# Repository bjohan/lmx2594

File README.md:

# lmx2594
Test board for lmx2594. The PCB is connected to an Arduino nano which then can be controlled from a PC. The Arduino can be programmed so that the PLL always starts with a certain frequency. It is also possible to change frequency dynamically.

# PCB
Current version of PCB in pcb/lmx2594_v2/

# Arduino sketch
In lmx2594NewSketch/

# Python library commandline tool
In py/ 
```
/lmx2594cmd2.py --help
usage: lmx2594.py [-h] [-f FREQUENCY] [-r REFERENCE] [-mo MASH_ORDER] [-m] [-l] port

Program for controlling lmx2594 pll

positional arguments:
  port                  For instance /dev/ttyUSB0

options:
  -h, --help            show this help message and exit
  -f FREQUENCY, --frequency FREQUENCY
                        Set frequency
  -r REFERENCE, --reference REFERENCE
                        Reference frequency
  -mo MASH_ORDER, --mash-order MASH_ORDER
                        Order of delta sigma
  -m, --macro           Record macro while setting frequency that will be executed at boot. This means that the device will set the specified frequency during power on even without a
                        computer
  -l, --locked          Check lock status

Have fun!
```

Example:

Program arduino so it always starts at 1296MHz with 10MHz reference
```
./lmx2594cmd2.py /dev/ttyUSB0 -r 10e6 -f 1296e6 -m
```

Example:

Set the frequency to 144MHz with 10MHz reference
```
./lmx2594cmd2.py /dev/ttyUSB0 -r 10e6 -f 144e6
```

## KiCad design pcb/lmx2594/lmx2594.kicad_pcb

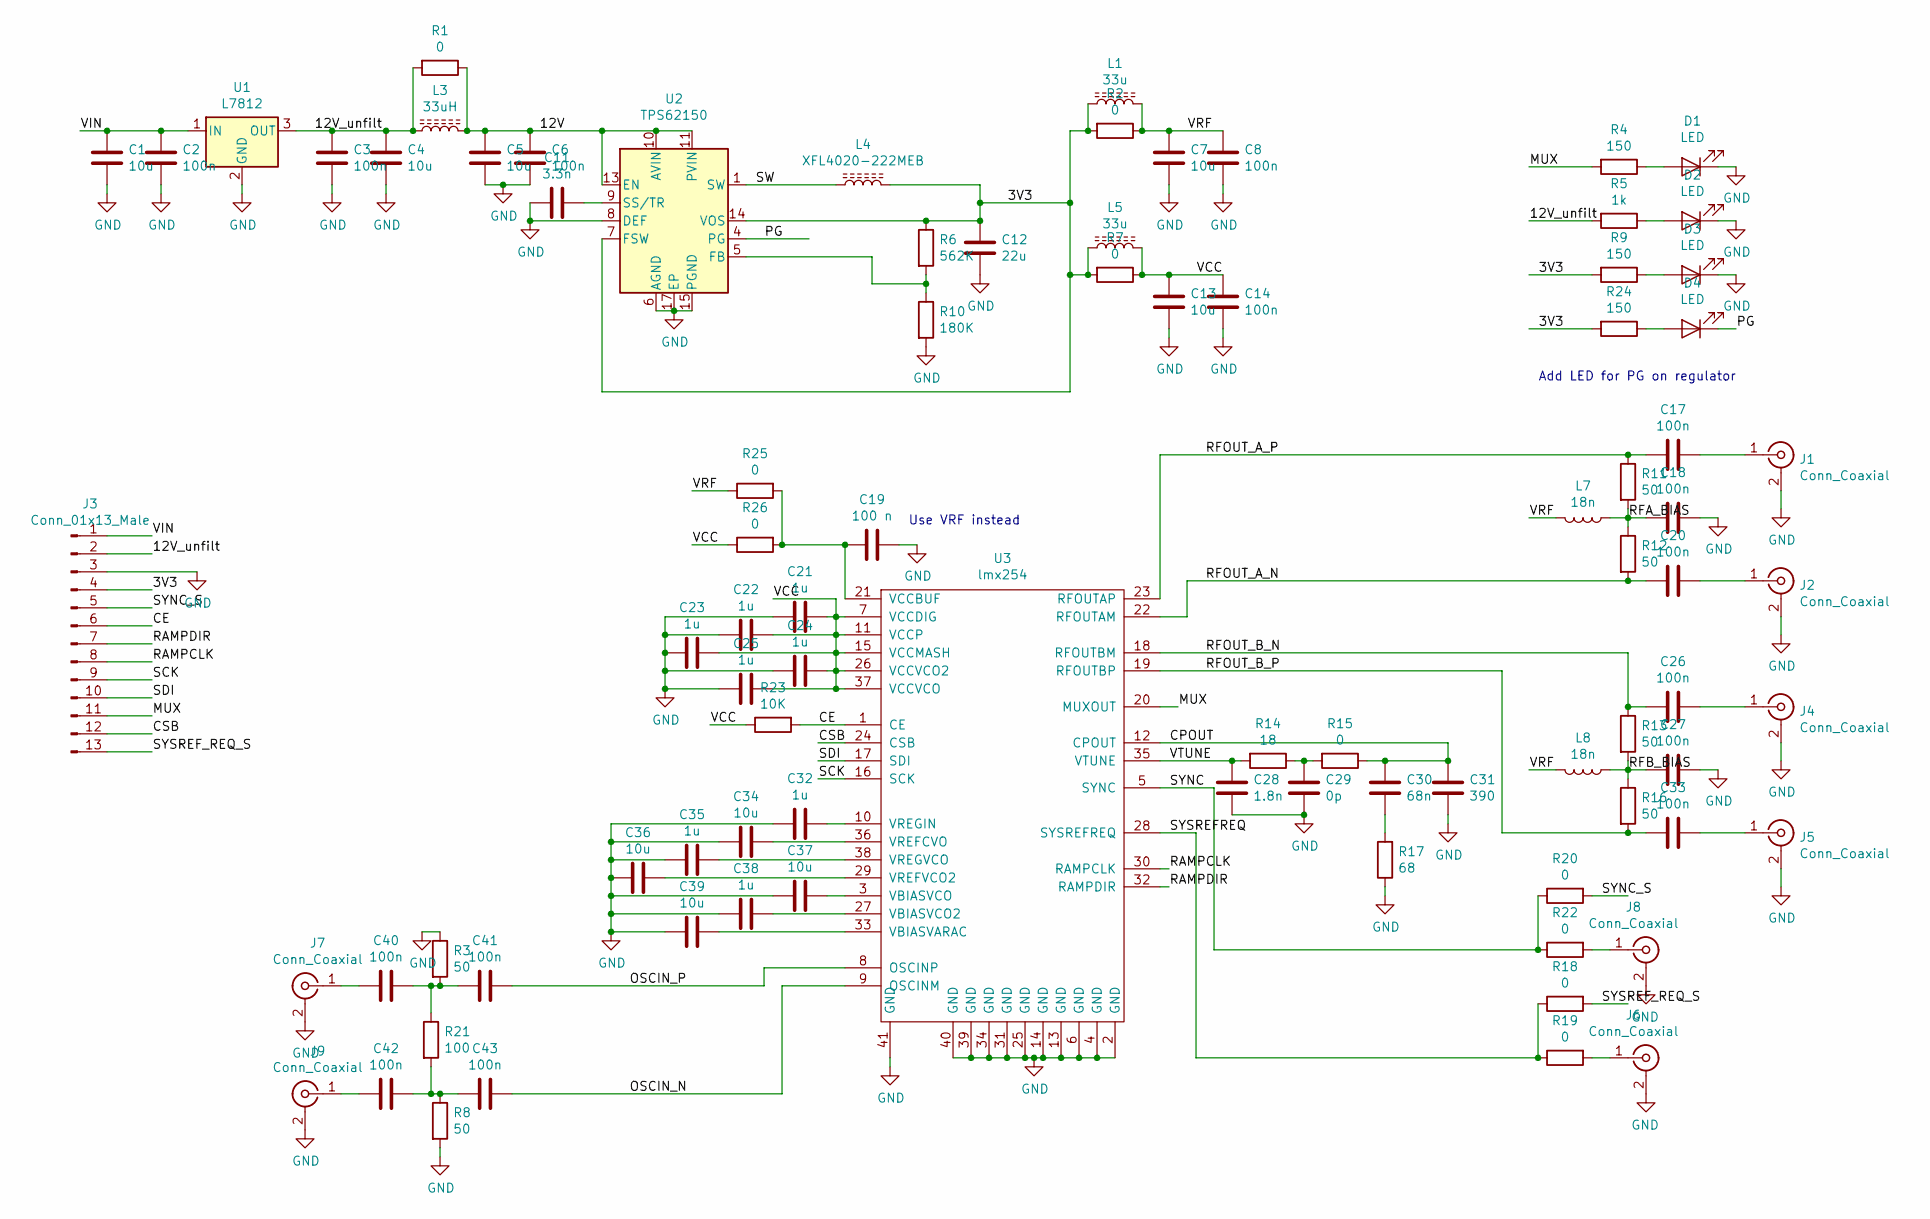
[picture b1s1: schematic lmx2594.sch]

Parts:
C1, C4, C5: 10u; C_1210_HandSoldering
C2, C3, C6, C8, C14, C17, C18, C20, C26, C27, C33, C40, C41, C42, C43: 100n; C_0603
C7, C13, C34, C36, C37, C39: 10u; C_0603
C11: 3.3n; C_0603
C12: 22u; C_0603
C19: 100 n; C_0603
C21, C22, C23, C24, C25, C32, C35, C38: 1u; C_0603
C28: 1.8n; C_0603
C29: 0p; C_0603
C30: 68n; C_0603
C31: 390; C_0603
D1, D2, D3, D4: LED; LED_0805_HandSoldering
J1, J2, J4, J5, J6, J7, J8, J9: Conn_Coaxial; SMA_THT_Jack_Straight
J3: Conn_01x13_Male; Molex_KK-6410-13_13x2.54mm_Straight
L1, L5: 33u; Neosid_Inductor_Ms95
L3: 33uH; Neosid_Inductor_Ms95
L4: XFL4020-222MEB; Inductor_Wurth_MAPI-4020
L7, L8: 18n; C_0603
R1, R2, R7, R15, R18, R19, R20, R22, R25, R26: 0; C_0603
R3, R8, R11, R12, R13, R16: 50; C_0603
R4, R9, R24: 150; C_0603
R5: 1k; C_0603
R6: 562K; C_0603
R10: 180K; C_0603
R14: 18; C_0603
R17: 68; C_0603
R21: 100; C_0603
R23: 10K; C_0603
U1: L7812; TO-220
U2: TPS62150; QFN-16-1EP_3x3mm_Pitch0.5mm_ThermalVias
U3: lmx254; Texas_PVQFN-N40

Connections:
/3V3: C12.1, J3.4, L1.1, L4.2, L5.1, R2.2, R6.1, R7.2, R9.2, R24.2, U2.7 (FSW), U2.14 (VOS)
/12V: C5.1, C6.1, L3.2, R1.1, U2.10 (AVIN), U2.11 (PVIN), U2.12 (PVIN), U2.13 (EN)
/12V_unfilt: C3.1, C4.1, J3.2, L3.1, R1.2, R5.2, U1.3 (OUT)
/CE: J3.6, R23.2, U3.1 (CE)
/CPOUT: C30.1, C31.1, R15.1, U3.12 (CPOUT)
/CSB: J3.12, U3.24 (CSB)
/MUX: J3.11, R4.2, U3.20 (MUXOUT)
/OSCIN_N: C43.1, U3.9 (OSCINM)
/OSCIN_P: C41.1, U3.8 (OSCINP)
/PG: D4.1 (K), U2.4 (PG)
/RAMPCLK: J3.8, U3.30 (RAMPCLK)
/RAMPDIR: J3.7, U3.32 (RAMPDIR)
/RFA_BIAS: C18.2, L7.1, R11.2, R12.1
/RFB_BIAS: C27.2, L8.1, R13.2, R16.1
/RFOUT_A_N: C20.2, R12.2, U3.22 (RFOUTAM)
/RFOUT_A_P: C17.2, R11.1, U3.23 (RFOUTAP)
/RFOUT_B_N: C26.2, R13.1, U3.18 (RFOUTBM)
/RFOUT_B_P: C33.2, R16.2, U3.19 (RFOUTBP)
/SCK: J3.9, U3.16 (SCK)
/SDI: J3.10, U3.17 (SDI)
/SW: L4.1, U2.1 (SW), U2.2 (SW), U2.3 (SW)
/SYNC: R20.1, R22.1, U3.5 (SYNC)
/SYNC_S: J3.5, R20.2
/SYSREFREQ: R18.1, R19.1, U3.28 (SYSREFREQ)
/SYSREF_REQ_S: J3.13, R18.2
/VCC: C13.1, C14.1, C21.1, C22.1, C23.1, C24.1, C25.1, L5.2, R7.1, R23.1, R26.1, U3.7 (VCCDIG), U3.11 (VCCP), U3.15 (VCCMASH), U3.26 (VCCVCO2), U3.37 (VCCVCO)
/VIN: C1.1, C2.1, J3.1, U1.1 (IN)
/VRF: C7.1, C8.1, L1.2, L7.2, L8.2, R2.1, R25.1
/VTUNE: C28.1, R14.2, U3.35 (VTUNE)
GND: C1.2, C2.2, C3.2, C4.2, C5.2, C6.2, C7.2, C8.2, C11.2, C12.2, C13.2, C14.2, C18.1, C19.1, C21.2, C22.2, C23.2, C24.2, C25.2, C27.1, C28.2, C29.2, C31.2, C32.2, C34.2, C35.2, C36.2, C37.2, C38.2, C39.2, D1.1 (K), D2.1 (K), D3.1 (K), J1.2 (Ext), J2.2 (Ext), J3.3, J4.2 (Ext), J5.2 (Ext), J6.2 (Ext), J7.2 (Ext), J8.2 (Ext), J9.2 (Ext), R3.1, R8.2, R10.2, R17.1, U1.2 (GND), U2.6 (AGND), U2.8 (DEF), U2.15 (PGND), U2.16 (PGND), U2.17 (EP), U3.2 (GND), U3.4 (GND), U3.6 (GND), U3.13 (GND), U3.14 (GND), U3.25 (GND), U3.31 (GND), U3.34 (GND), U3.39 (GND), U3.40 (GND), U3.41 (GND)
unnamed: C11.1, U2.9 (SS/TR)
unnamed: C17.1, J1.1 (In)
unnamed: C19.2, R25.2, R26.2, U3.21 (VCCBUF)
unnamed: C20.1, J2.1 (In)
unnamed: C26.1, J4.1 (In)
unnamed: C29.1, R14.1, R15.2
unnamed: C30.2, R17.2
unnamed: C32.1, U3.10 (VREGIN)
unnamed: C33.1, J5.1 (In)
unnamed: C34.1, U3.36 (VREFCVO)
unnamed: C35.1, U3.38 (VREGVCO)
unnamed: C36.1, U3.29 (VREFVCO2)
unnamed: C37.1, U3.3 (VBIASVCO)
unnamed: C38.1, U3.27 (VBIASVCO2)
unnamed: C39.1, U3.33 (VBIASVARAC)
unnamed: C40.1, C41.2, R3.2, R21.1
unnamed: C40.2, J7.1 (In)
unnamed: C42.1, C43.2, R8.1, R21.2
unnamed: C42.2, J9.1 (In)
unnamed: D1.2 (A), R4.1
unnamed: D2.2 (A), R5.1
unnamed: D3.2 (A), R9.1
unnamed: D4.2 (A), R24.1
unnamed: J6.1 (In), R19.2
unnamed: J8.1 (In), R22.2
unnamed: R6.2, R10.1, U2.5 (FB)

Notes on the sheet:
Add LED for PG on regulator
Use VRF instead

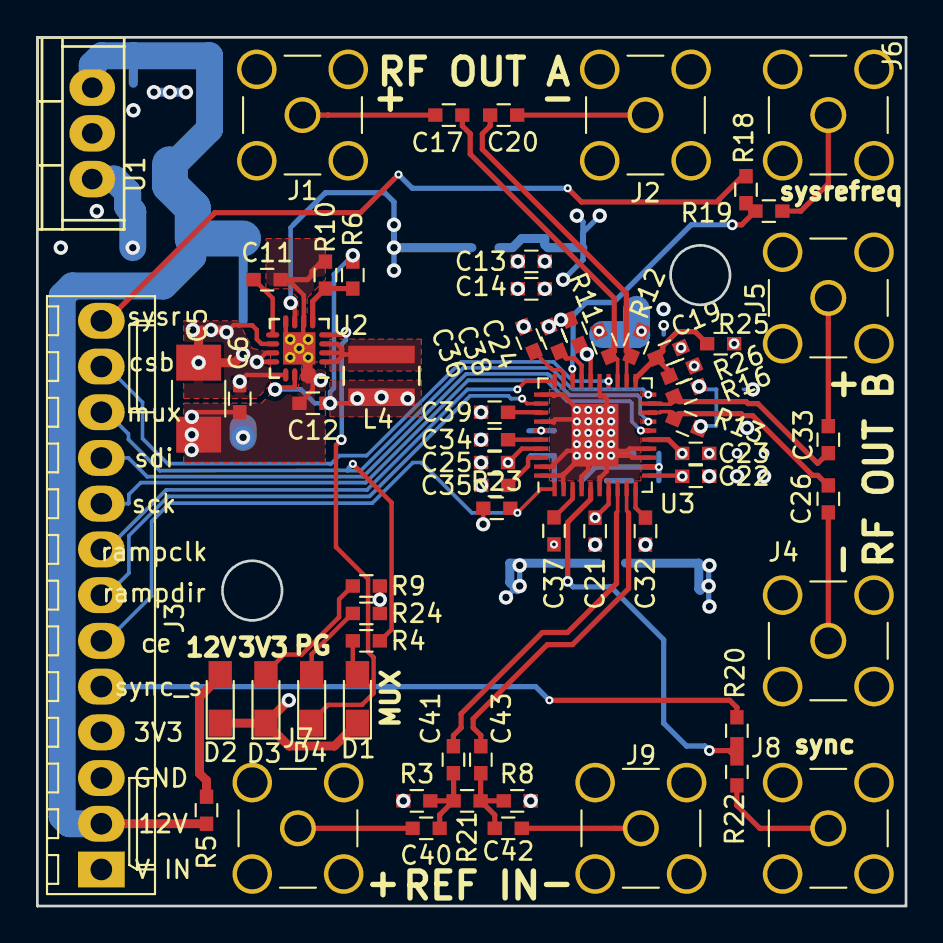
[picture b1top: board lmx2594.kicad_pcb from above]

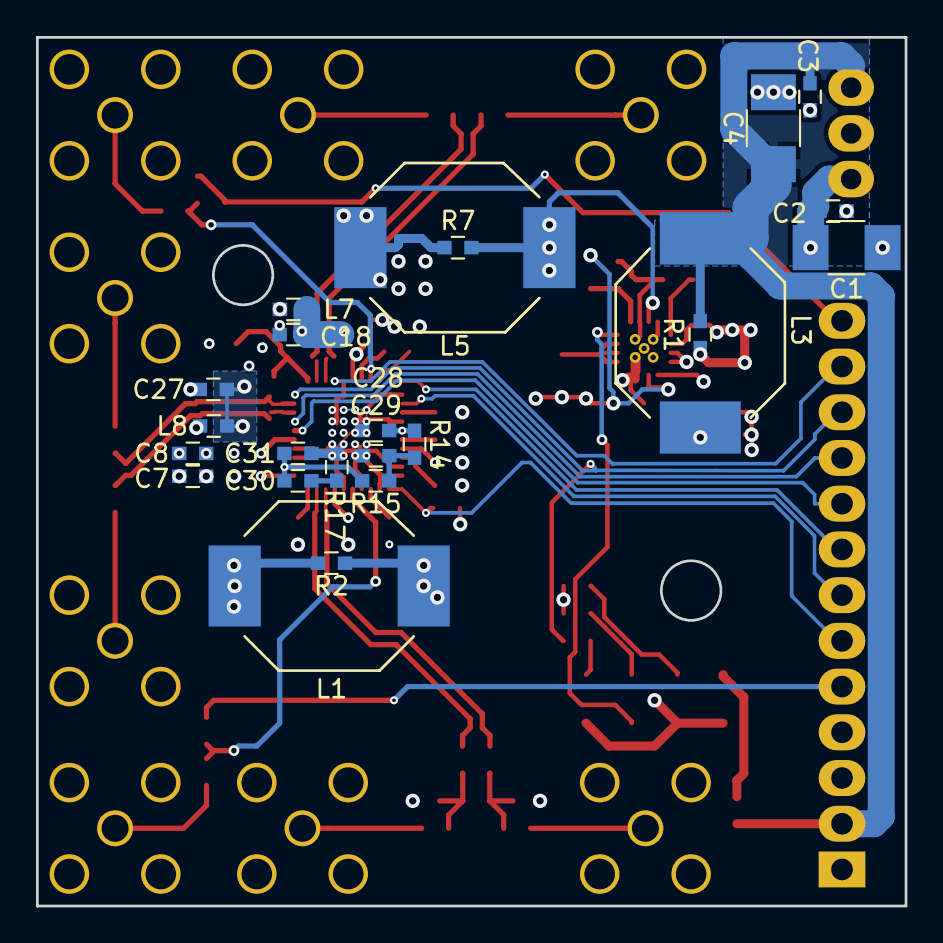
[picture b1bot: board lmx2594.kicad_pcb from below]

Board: 4 copper layers, 48.3 x 48.3 mm, 87 parts (23 on the bottom side), 56 nets.

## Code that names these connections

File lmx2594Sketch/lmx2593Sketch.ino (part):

#define SYSREF 5
#define CSB 6
#define MUX 7
#define SDI_DATA_OUT 8
#define SCK 9
#define RAMPCLK 10
#define RAMPDIR 11
#define CE 12
#define SYNC 13

#define REGISTER_R0 0b0010010000010000
#define REGISTER_R1 0b0000100000001000
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	Serial.begin(115200);
	// initialize the digital pin as an output.
	pinMode(SYSREF, OUTPUT);
	pinMode(CSB, OUTPUT);
	pinMode(MUX, INPUT);
	pinMode(SDI_DATA_OUT, OUTPUT);
	pinMode(SCK, OUTPUT);
	pinMode(RAMPCLK, OUTPUT);
	pinMode(RAMPDIR, OUTPUT);
	pinMode(CE, OUTPUT);
	pinMode(SYNC, OUTPUT);
	digitalWrite(CSB, HIGH);
	Serial.println("CE LOW");
	digitalWrite(CE, LOW);
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
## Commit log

2019-05-04 schematic done, started placing components
2019-05-05 More work on layout
2019-05-05 All signals routed DRC pass but needs to be tidied up
2019-05-05 Layout sort is probably done, can make something nicer with powerplanes but i do not think it is needed. Silkscreen must also be fixed
2019-05-06 Added single ended terminations to osci
2019-05-06 Tidying up a bit and added pullup on CE
2019-05-06 More review of schematic
2019-06-07 Review, fixed vbuf and added pg led
2019-06-07 additional fixes to silkscreen
2019-12-10 Fixed diff pair impedance
2020-02-20 control code
2020-08-16 added v2
2020-08-17 Librarized code slightly
2020-08-20 Now seems to work
2022-06-21 added cmd version of python script
2022-09-28 Added wait for user input
2022-11-22 Added new arduino FW
2022-11-22 Added new script
2022-11-22 cleaned up some prints
2022-11-23 Removed some more spurious prints
2022-11-23 Made large array static so the sketch wil run on m168
2022-11-23 Added replay of macro at boot...
2022-12-11 Arranging files
2022-12-11 Moved verification measurements
2022-12-11 updated library
2022-12-11 Added measurements
2022-12-11 Added data repo
2022-12-11 Removed accidentaly added recursive submodule
2022-12-12 Added smal wrapper for yig filter class so that partially populated board can be used to generate high resolution DC voltages
2022-12-13 Tested voltage generator
2022-12-13 Started working on vga-test
2022-12-18 Added measurements of vga and attenuator
2022-12-18 Added some measurements of sweeper frequency and power level in preparation of detector testing
2022-12-18 Measured directional detectors
2022-12-19 Added measurement data for modeling test voltage generator
2023-05-03 Added plot and bom
2023-05-20 Added gitignore and removed prints, fixed bug for output power
2023-05-20 Added small tool to convert ti config to python dicts, and made class independent of old .txt-file for config
2023-05-21 Added gpio-support to control external relays. Removed old code, made commandbuffer lagerger
2023-05-21 Removed prints and set mux to correct values
2023-05-21 Updated gitignore
2024-07-04 Added README
2024-10-01 Create LICENSE
2024-11-23 Updated schematic to KiCad 7.0. Note that layout etc has not been updated yet
2025-07-26 Do not use doubler if fref < 20MHz
2026-04-28 Quick fix for lock failure with high reference input
2026-04-28 Added rudimentary support for 2595
